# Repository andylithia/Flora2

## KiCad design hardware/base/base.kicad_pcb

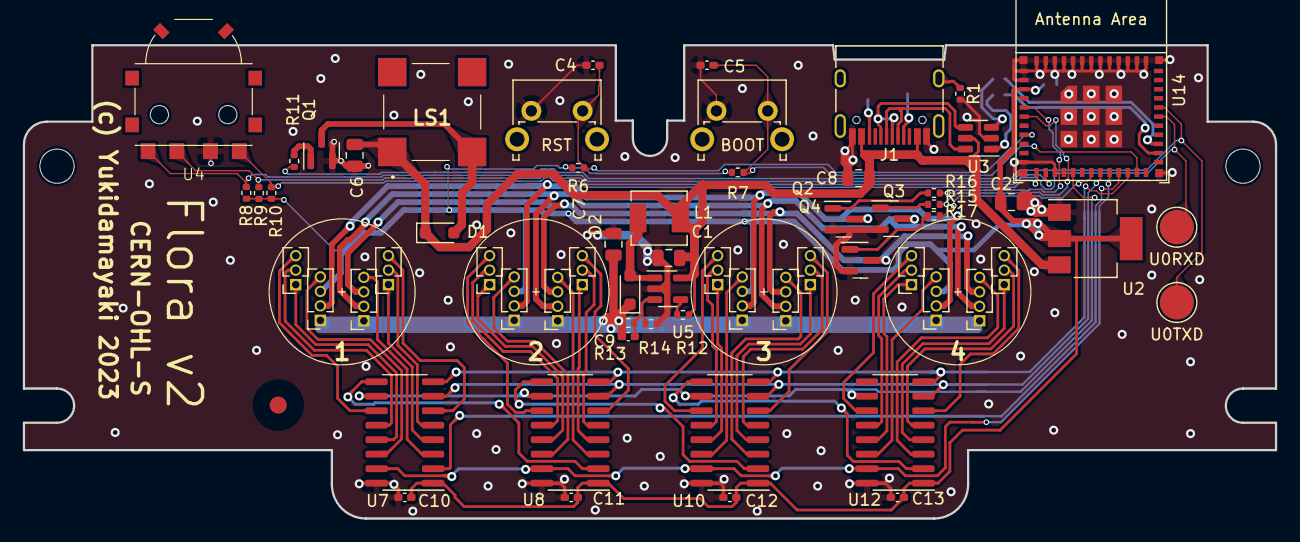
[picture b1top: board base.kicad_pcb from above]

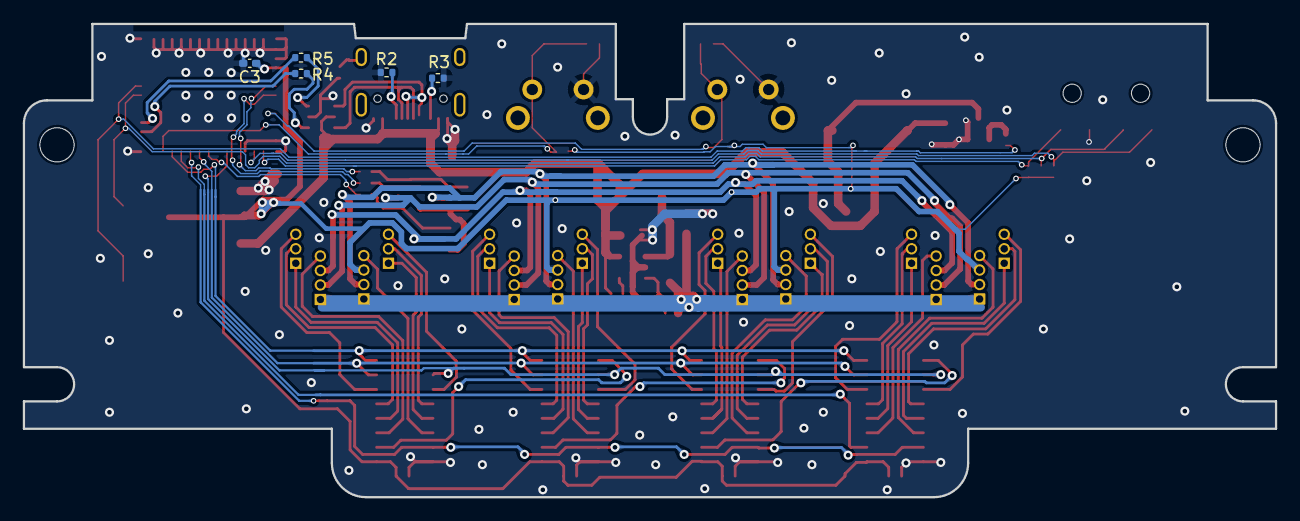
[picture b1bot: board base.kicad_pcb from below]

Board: 2 copper layers, 109.8 x 41.5 mm, 56 parts (5 on the bottom side), 73 nets.

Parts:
C1, C2, C6, C7, C8: 1uF; C_0805_2012Metric
C3, C4, C5, C10, C11, C12, C13: 100nF; C_0402_1005Metric_Pad0.74x0.62mm_HandSolder
C9: 220pF; C_0402_1005Metric_Pad0.74x0.62mm_HandSolder
D1, D2: SOD323; D_SOD-323_HandSoldering
J1: USB_C_Receptacle_USB2.0; USB_C_Receptacle_HRO_TYPE-C-31-M-12
L1: 6.8uH; L_Sunlord_MWSA0402S
LS1: CMT-8503-85B-SMT-TR; CMT850385BSMTTR
Q1, Q2, Q3, Q4: 2N7002; SOT-23
R1: 0; R_0402_1005Metric
R2, R3: 5.1K; R_0402_1005Metric
R4, R5: 22; R_0402_1005Metric
R6, R7, R8, R9, R10, R14: 10K; R_0402_1005Metric
R11, R15, R16, R17: 20; R_0402_1005Metric
R12: 1M; R_0402_1005Metric
R13: 22K; R_0402_1005Metric
SW1: RST; SW_Tactile_SPST_Angled_PTS645Vx83-2LFS
SW2: BOOT; SW_Tactile_SPST_Angled_PTS645Vx83-2LFS
TP1: U0RXD; TestPoint_Pad_D3.0mm
TP2: U0TXD; TestPoint_Pad_D3.0mm
U2: LD1117S33TR_SOT223; SOT-223-3_TabPin2
U3: WE-TVS-82400102; SOT-23-6
U4: MITSUMI_SIQ-02FVS3
U5: LMR62421XMF; SOT-23-5
U6, U9, U11, U13: Kartusche IV9; Kartusche_IV9
U7, U8, U10, U12: TPIC6C595 / TLC6C598; SOIC-16_3.9x9.9mm_P1.27mm
U14: ESP32-C3-MINI-1

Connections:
+3.3V: C2.1, C3.1, C10.1, C11.1, C12.1, C13.1, R6.2, R7.2, R8.2, R9.2, R10.2, U2.2 (VO), U6.12 (ACOM_LED), U7.1 (VCC), U8.1 (VCC), U9.12 (ACOM_LED), U10.1 (VCC), U11.12 (ACOM_LED), U12.1 (VCC), U13.12 (ACOM_LED), U14.3 (3V3)
+4V: C7.1, C9.1, D2.1 (K), R13.2, U6.1 (ACOM_IV9), U6.14 (ACOM_IV9), U9.1 (ACOM_IV9), U9.14 (ACOM_IV9), U11.1 (ACOM_IV9), U11.14 (ACOM_IV9), U13.1 (ACOM_IV9), U13.14 (ACOM_IV9)
+5V: C1.1, C6.1, C8.1, D1.1 (K), J1.A4 (VBUS), J1.A9 (VBUS), J1.B4 (VBUS), J1.B9 (VBUS), L1.1, LS1.1 (+), R12.2, U2.3 (VI), U3.5, U5.5 (VIN)
/DIM: U7.8 (~G), U8.8 (~G), U10.8 (~G), U12.8 (~G), U14.22 (GPIO8)
/IV9/KB_SINK: Q2.3 (D), U6.13 (KB), U9.13 (KB), U11.13 (KB), U13.13 (KB)
/IV9/KG_SINK: Q3.3 (D), U6.2 (KG), U9.2 (KG), U11.2 (KG), U13.2 (KG)
/IV9/KR_SINK: Q4.3 (D), U6.3 (KR), U9.3 (KR), U11.3 (KR), U13.3 (KR)
/IV9_~RST: U7.7 (~CLR), U8.7 (~CLR), U10.7 (~CLR), U12.7 (~CLR), U14.19 (GPIO5/ADC2_CH0)
/LATCH: U7.10 (RCK), U8.10 (RCK), U10.10 (RCK), U12.10 (RCK), U14.16 (GPIO10)
/LED_KB: R16.1, U14.5 (GPIO2/ADC1_CH2)
/LED_KG: R15.1, U14.6 (GPIO3/ADC1_CH3)
/LED_KR: R17.1, U14.18 (GPIO4/ADC1_CH4)
/SCK: U7.15 (SRCK), U8.15 (SRCK), U10.15 (SRCK), U12.15 (SRCK), U14.20 (GPIO6)
/SD: U7.2 (SER_IN), U14.21 (GPIO7)
/~BOOT: C5.1, R7.1, SW2.2, U14.23 (GPIO9)
/~RST: C4.1, R6.1, SW1.2, U14.8 (EN/CHIP_PU)
GND: C1.2, C2.2, C3.2, C4.2, C5.2, C6.2, C7.2, C8.2, C10.2, C11.2, C12.2, C13.2, J1.A1 (GND), J1.A12 (GND), J1.B1 (GND), J1.B12 (GND), Q1.2 (S), Q2.2 (S), Q3.2 (S), Q4.2 (S), R1.2, R2.1, R3.1, R14.1, SW1.1, SW2.1, U2.1 (GND), U3.2, U4.C (Com), U5.2 (GND), U7.16 (GND), U8.16 (GND), U10.16 (GND), U12.16 (GND), U14.1 (GND), U14.2 (GND), U14.11 (GND), U14.14 (GND), U14.36 (GND), U14.37 (GND), U14.38 (GND), U14.39 (GND), U14.40 (GND), U14.41 (GND), U14.42 (GND), U14.43 (GND), U14.44 (GND), U14.45 (GND), U14.46 (GND), U14.47 (GND), U14.48 (GND), U14.49 (GND), U14.50 (GND), U14.51 (GND), U14.52 (GND), U14.53 (GND)
unnamed: D1.2 (A), LS1.MP1, Q1.3 (D)
unnamed: D2.2 (A), L1.2, U5.1 (SW)
unnamed: J1.A5 (CC1), R2.2
unnamed: J1.B5 (CC2), R3.2
unnamed: J1.A6 (D+), J1.B6 (D+), U3.4
unnamed: J1.A7 (D-), J1.B7 (D-), U3.6
unnamed: J1.S1 (SHIELD), R1.1
unnamed: Q1.1 (G), R11.1
unnamed: Q2.1 (G), R16.2
unnamed: Q3.1 (G), R15.2
unnamed: Q4.1 (G), R17.2
unnamed: R4.1, U3.1
unnamed: R5.1, U3.3
unnamed: R12.1, U5.4 (EN)
unnamed: C9.2, R13.1, R14.2, U5.3 (FB)
unnamed: U6.5 (K2), U7.4 (DRAIN1)
unnamed: U6.6 (K3), U7.5 (DRAIN2)
unnamed: U6.7 (K4), U7.6 (DRAIN3)
unnamed: U6.4 (K5), U7.3 (DRAIN0)
unnamed: U6.11 (K6), U7.14 (DRAIN7)
unnamed: U6.8 (K7), U7.11 (DRAIN4)
unnamed: U6.9 (K8), U7.12 (DRAIN5)
unnamed: U6.10 (K9), U7.13 (DRAIN6)
unnamed: U7.9 (SER_OUT), U8.2 (SER_IN)
unnamed: U8.3 (DRAIN0), U9.4 (K5)
unnamed: U8.4 (DRAIN1), U9.5 (K2)
unnamed: U8.5 (DRAIN2), U9.6 (K3)
unnamed: U8.6 (DRAIN3), U9.7 (K4)
unnamed: U8.11 (DRAIN4), U9.8 (K7)
unnamed: U8.12 (DRAIN5), U9.9 (K8)
unnamed: U8.13 (DRAIN6), U9.10 (K9)
unnamed: U8.14 (DRAIN7), U9.11 (K6)
unnamed: U10.3 (DRAIN0), U11.4 (K5)
unnamed: U10.4 (DRAIN1), U11.5 (K2)
unnamed: U10.5 (DRAIN2), U11.6 (K3)
unnamed: U10.6 (DRAIN3), U11.7 (K4)
unnamed: U10.11 (DRAIN4), U11.8 (K7)
unnamed: U10.12 (DRAIN5), U11.9 (K8)
unnamed: U10.13 (DRAIN6), U11.10 (K9)
unnamed: U10.14 (DRAIN7), U11.11 (K6)
unnamed: U8.9 (SER_OUT), U10.2 (SER_IN)
unnamed: U10.9 (SER_OUT), U12.2 (SER_IN)
unnamed: U12.3 (DRAIN0), U13.4 (K5)
unnamed: U12.4 (DRAIN1), U13.5 (K2)
unnamed: U12.5 (DRAIN2), U13.6 (K3)
unnamed: U12.6 (DRAIN3), U13.7 (K4)
unnamed: U12.11 (DRAIN4), U13.8 (K7)
unnamed: U12.12 (DRAIN5), U13.9 (K8)
unnamed: U12.13 (DRAIN6), U13.10 (K9)
unnamed: U12.14 (DRAIN7), U13.11 (K6)
unnamed: R10.1, U4.B, U14.12 (GPIO0/ADC1_CH0/XTAL_32K_P)
unnamed: R8.1, U4.A, U14.13 (GPIO1/ADC1_CH1/XTAL_32K_N)
unnamed: R4.2, U14.26 (GPIO18/USB_D-)
unnamed: R5.2, U14.27 (GPIO19/USB_D+)
unnamed: R9.1, TP1.1, U4.S (Sw), U14.30 (GPIO20/U0RXD)
unnamed: R11.2, TP2.1, U14.31 (GPIO21/U0TXD)

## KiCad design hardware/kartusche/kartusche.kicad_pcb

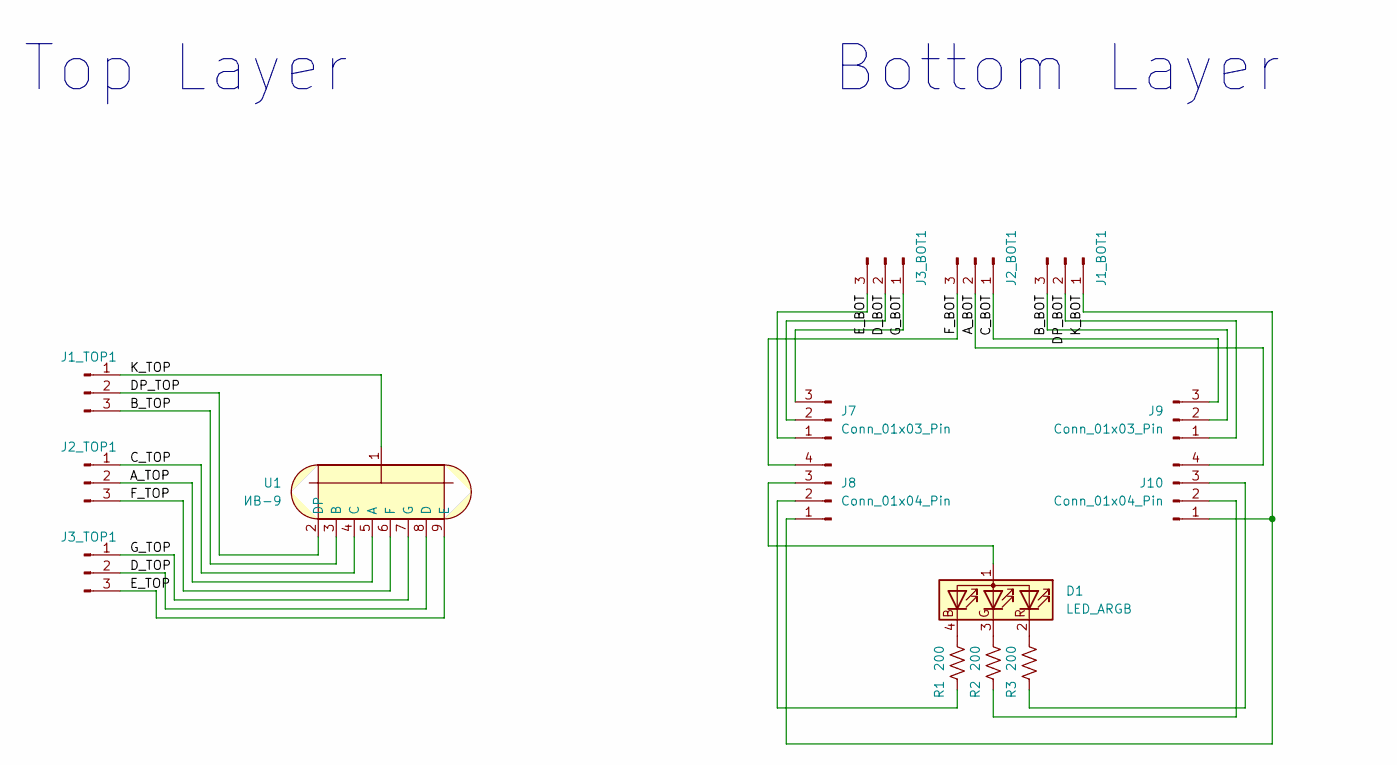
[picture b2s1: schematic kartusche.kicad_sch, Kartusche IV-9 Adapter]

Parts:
D1: LED_ARGB; LED_LiteOn_LTST-C19HE1WT
J1_BOT1, J1_TOP1, J2_BOT1, J2_TOP1, J3_BOT1, J3_TOP1, J7, J9: Conn_01x03_Pin; PinHeader_1x03_P1.27mm_Vertical
J8, J10: Conn_01x04_Pin; PinHeader_1x04_P1.27mm_Vertical
R1, R2, R3: 200; R_0402_1005Metric
U1: ИВ-9; IV9

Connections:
/A_BOT: J2_BOT1.2, J10.4
/A_TOP: J2_TOP1.2, U1.5 (A)
/B_BOT: J1_BOT1.3, J9.2
/B_TOP: J1_TOP1.3, U1.3 (B)
/C_BOT: J2_BOT1.1, J9.3
/C_TOP: J2_TOP1.1, U1.4 (C)
/DP_BOT: J1_BOT1.2, J9.1
/DP_TOP: J1_TOP1.2, U1.2 (DP)
/D_BOT: J3_BOT1.2, J7.2
/D_TOP: J3_TOP1.2, U1.8 (D)
/E_BOT: J3_BOT1.3, J7.1
/E_TOP: J3_TOP1.3, U1.9 (E)
/F_BOT: J2_BOT1.3, J8.4
/F_TOP: J2_TOP1.3, U1.6 (F)
/G_BOT: J3_BOT1.1, J7.3
/G_TOP: J3_TOP1.1, U1.7 (G)
/K_BOT: J1_BOT1.1, J8.1, J10.1
/K_TOP: J1_TOP1.1, U1.1
unnamed: D1.1 (A), J8.3
unnamed: D1.4 (BK), R1.1
unnamed: D1.3 (GK), R2.1
unnamed: D1.2 (RK), R3.1
unnamed: J8.2, R1.2
unnamed: J10.2, R2.2
unnamed: J10.3, R3.2

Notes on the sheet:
Top Layer
Bottom Layer

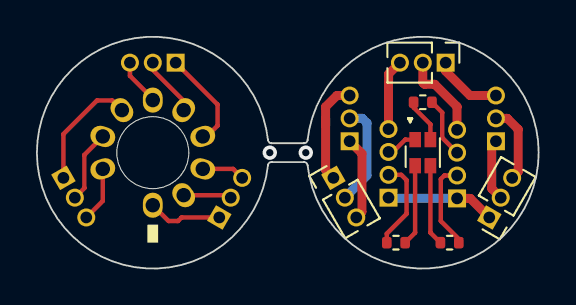
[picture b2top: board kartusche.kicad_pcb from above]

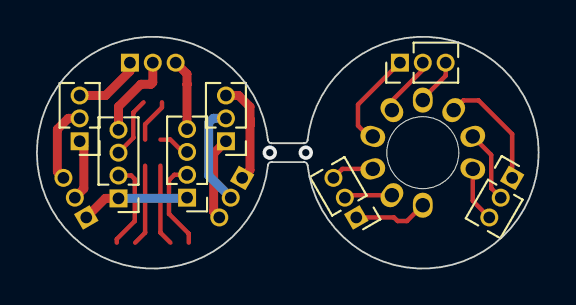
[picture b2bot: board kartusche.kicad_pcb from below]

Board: 2 copper layers, 27.9 x 12.9 mm, 15 parts (7 on the bottom side), 25 nets.

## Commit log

2023-12-08 Starting Flora2 Project
2023-12-08 Finishing Top Schematic
2023-12-08 Base PCB WIP
2023-12-08 Minor
2023-12-10 Base V2 Done
2023-12-22 Base PCB Bugfix

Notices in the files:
hardware/base/base.kicad_pcb:
CERN-OHL-S
hardware/kartusche/kartusche.kicad_pcb:
Copyright 2023 AnalogMiko
This source describes Open Hardware and is licensed under the CERN-OHL-S v2.
